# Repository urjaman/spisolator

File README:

SPI Isolator
------------

This is a PCB for allowing arbitrary motherboards
to have their SPI flash chip isolated from the
motherboard when powered off (or via control signal), 
to allow external (ISP) programming.

KiCad sources are in the repo, but
for simple purchasing, there's the PCB shared in oshpark:
https://oshpark.com/shared_projects/ZljIshjt

And the parts list:		- Example URLs
R1, R2: 4k7 0805 resistor	- http://uk.farnell.com/walsin/wr08x4701ftl/res-thick-film-4k7-1-150v-0805/dp/2502731
C1: 1u 0805 capacitor		- http://uk.farnell.com/kemet/c0805c105z3vactu/ceramic-capacitor-1uf-25v-y5v/dp/1269997
D1: schottky SOD-323 diode	- http://uk.farnell.com/nxp/pmeg2005aea/diode-schottky-sod-323/dp/8737843
U1: 74LVC4066			- http://uk.farnell.com/on-semiconductor/mc74lvxt4066dr2g/analogue-switch-quad-spst-nsoic/dp/2464564 , http://eu.mouser.com/ProductDetail/NXP-Semiconductors/74LVC4066D118
P2: 2x4 IDC header		- http://uk.farnell.com/te-connectivity-amp/826942-4/header-straight-2x4way/dp/1248160
U2: SO-8 SPI flash chip		- http://uk.farnell.com/spansion/s25fl164k0xmfi011/ic-memory-flash-64mbit-soic-8/dp/2363323

Oh, and if you like this, pizza money donations are accepted via paypal:
urjaman at gmail dot com.

Known unsupported: Quad I/O. If you have a motherboard that needs that, message me,
for a small donation I could make a version that supports Quad I/O ;)

Build Howto and Usage (beta, untested)
--------------------------------------
solder the components on the PCB, a probably fine order is
starting from the underside first...
remove the flash chip from the target machine, and attach the
PCB as near as possible to its layout (maybe with double-sided tape),
but not over the layout.
Connect small (patch, "green wire") wires from the 6 places
on the edge of the PCB to the layout

the 2x4 ISP connector is compatible with the one in the PC Engines
APU series, so if you have an ISP lead for them, it should work
for this, otherwise, the pinout is:
3V3 1 2 GND
!CS 3 4 SCK
 SO 5 6 SI
--  7 8 buffer en/!dis

NOTE: The 160129 version was not compatible with the APU pinout
(which is a dediprog programming pinout), the MOSI and MISO were accidentally
swapped.

The analog switch/buffer is normally controlled by 
the 3V3 power on the motherboard, so the chip is externally
programmable when the motherboard 3.3V supply is OFF

The buffer control line is an extension to the APU
connector (it had nothing there), that can be used 
to program externally even if the target motherboard
is running. To do that, connect pin 8 of the ISP header to ground,
but preferably not too hard;
if you connect the header the wrong way around and there is some other
ground connection between the programmer and the motherboard (eg. RS232),
this would connect the 3V3 line to ground.
So a suggested safer circuit is:

pin 8 - 50 ohm - switch - pin 2 

With parts for this extension:
http://uk.farnell.com/multicomp/mcknp03uj0500b00/resistor-wirewound-50r-5-3w/dp/1903828
http://uk.farnell.com/multicomp/mcr13-5-05/switch-toggle-spst-off-on-so/dp/2128120

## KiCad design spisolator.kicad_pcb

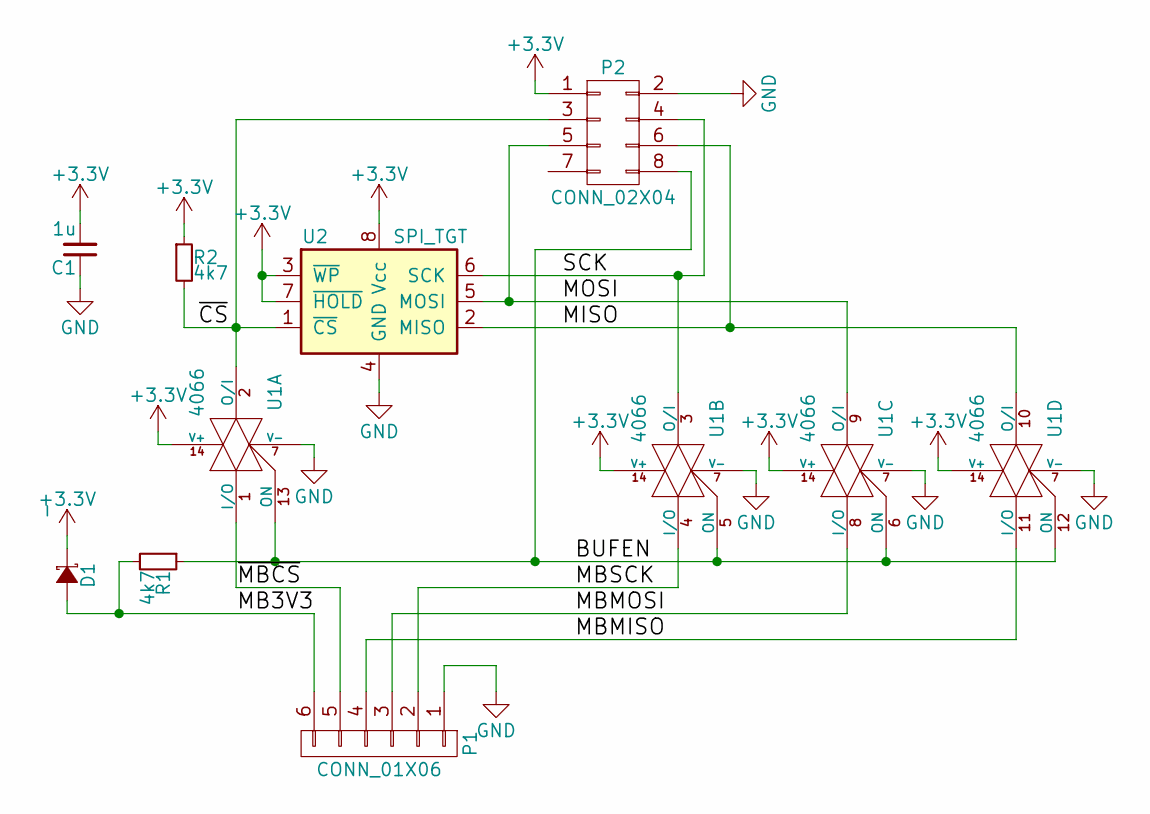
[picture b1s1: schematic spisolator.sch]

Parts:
C1: 1u; C_0805_HandSoldering
D1: -; SOD-323
P1: CONN_01X06; Socket_Strip_Straight_1x06
P2: CONN_02X04; Pin_Header_Straight_2x04
R1, R2: 4k7; R_0805_HandSoldering
U1: 4066; SOIC-14_N
U2: SPI_TGT; SOIC-8_3.9x4.9mm_Pitch1.27mm

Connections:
+3V3: C1.2, D1.1 (K), P2.1, R2.1, U1.14 (V+), U2.3 (~WP), U2.7 (~HOLD), U2.8 (Vcc)
/BUFEN: P2.8, R1.1, U1.5 (ON), U1.6 (ON), U1.12 (ON), U1.13 (ON)
/MB3V3: D1.2 (A), P1.6, R1.2
/MBMISO: P1.4, U1.11 (I/O)
/MBMOSI: P1.3, U1.8 (I/O)
/MBSCK: P1.2, U1.4 (I/O)
/MISO: P2.6, U1.10 (O/I), U2.2 (MISO)
/MOSI: P2.5, U1.9 (O/I), U2.5 (MOSI)
/SCK: P2.4, U1.3 (O/I), U2.6 (SCK)
/~CS: P2.3, R2.2, U1.2 (O/I), U2.1 (~CS)
/~MBCS: P1.5, U1.1 (I/O)
GND: C1.1, P1.1, P2.2, U1.7 (V-), U2.4 (GND)

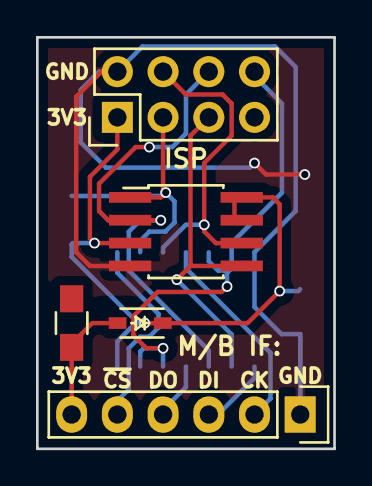
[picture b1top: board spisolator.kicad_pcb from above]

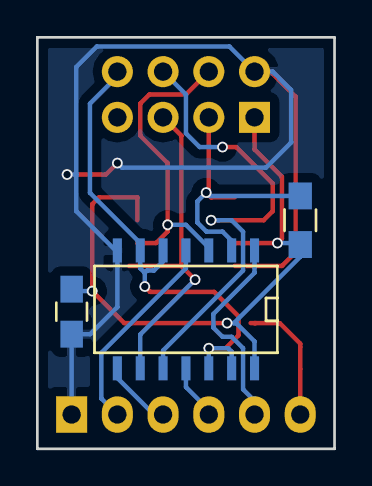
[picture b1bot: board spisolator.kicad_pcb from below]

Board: 2 copper layers, 16.5 x 22.9 mm, 8 parts (3 on the bottom side), 12 nets.

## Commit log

2016-01-28 Initial commit, only the build requirements for this project
2016-01-28 add the diode to the parts list
2016-01-28 fix the URLs to ones that have a sane MoQ
2016-01-29 More build info, better parts numbers
2016-01-29 new oshpark link
2016-01-29 new part positions for the new pcb
2016-02-03 kicad sources for the SPI Isolator, and the gerber files
2016-02-03 to be released stuff, r2 of the PCB
2016-02-03 Change the state of the project to really open sourced
    And included my paypal, just in case somebody wants to give me money still
2017-08-10 Fix swapped MISO/MOSI in the programming connector
